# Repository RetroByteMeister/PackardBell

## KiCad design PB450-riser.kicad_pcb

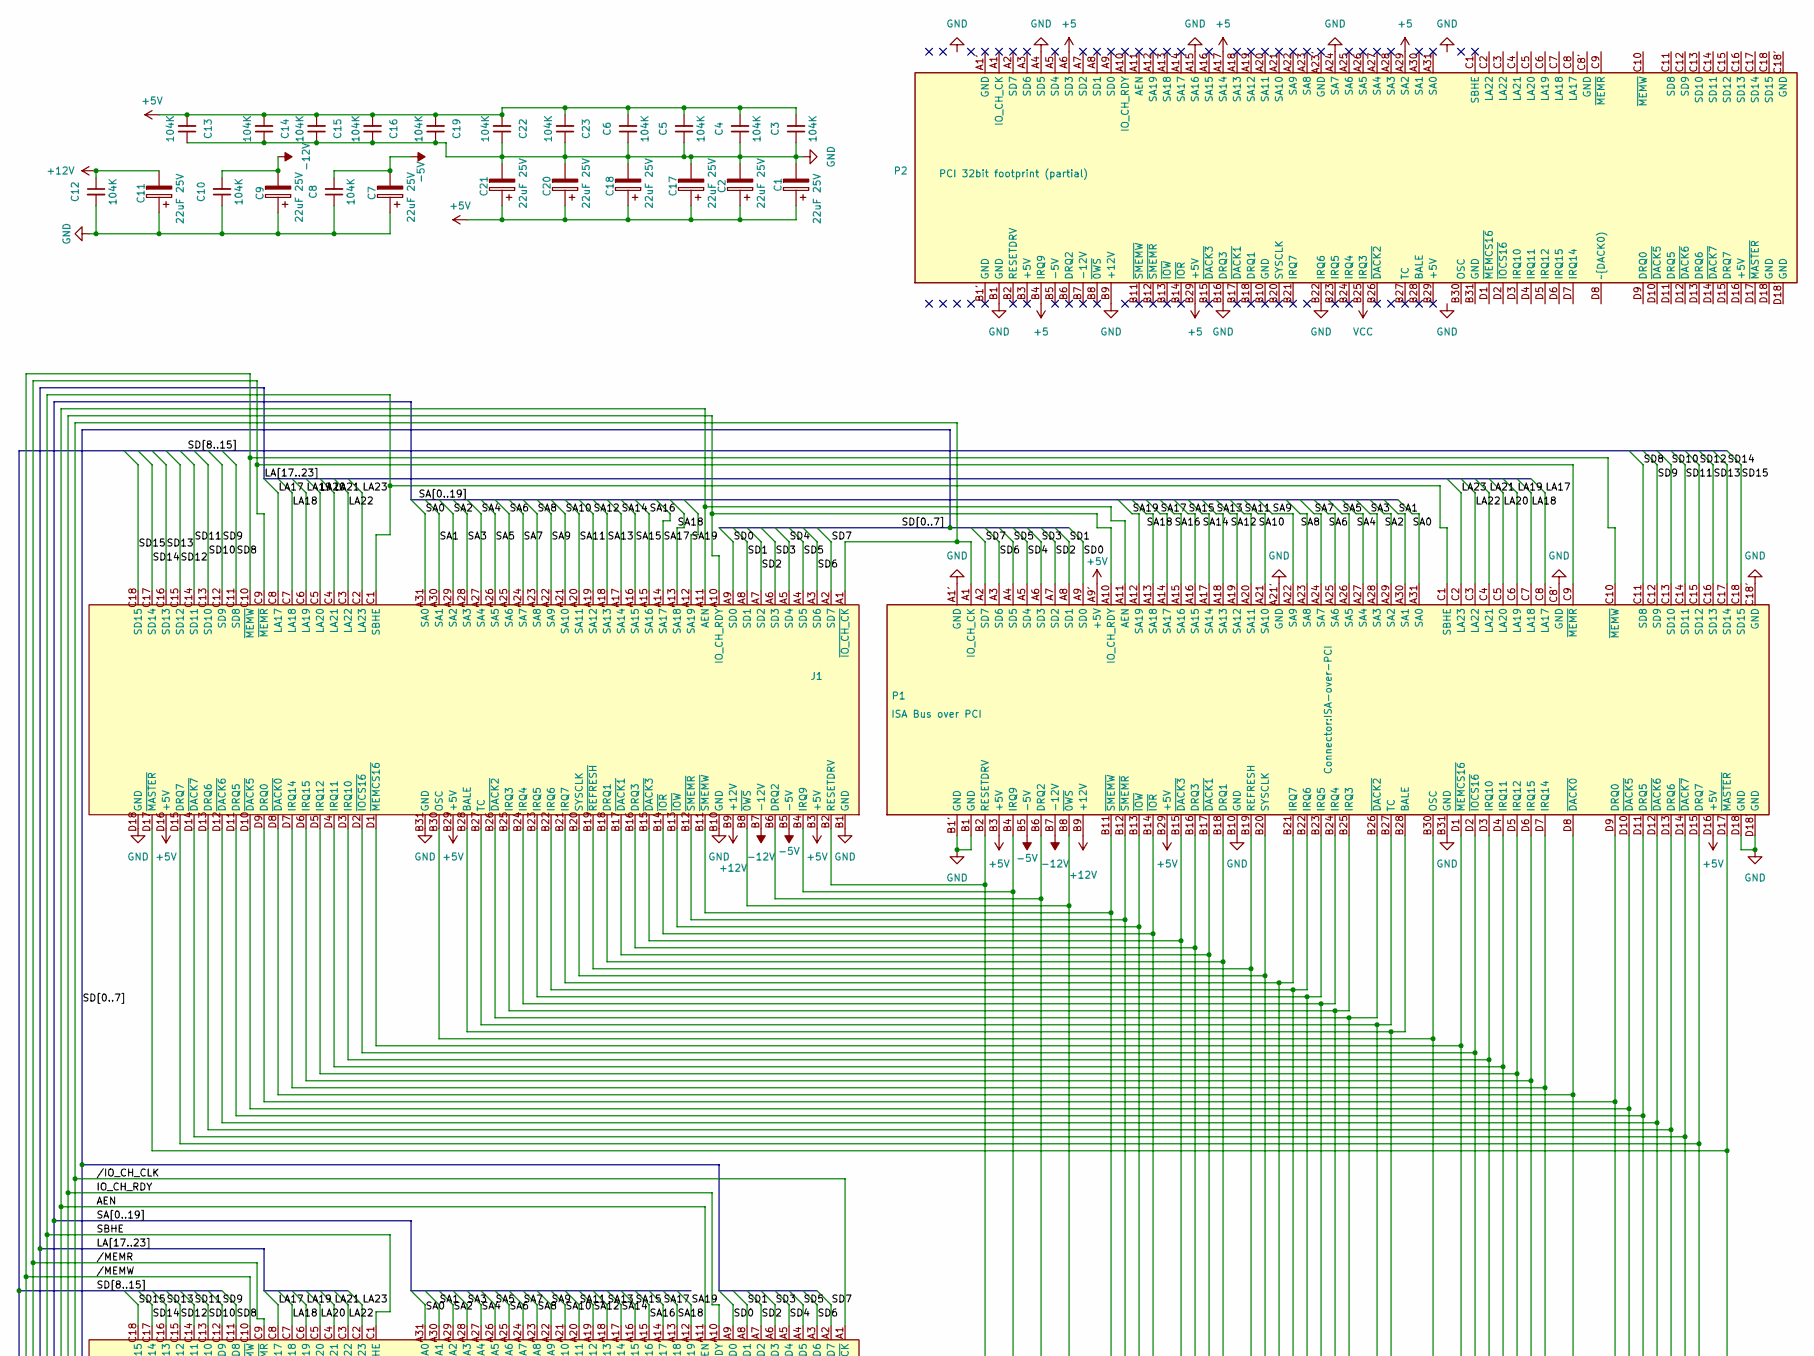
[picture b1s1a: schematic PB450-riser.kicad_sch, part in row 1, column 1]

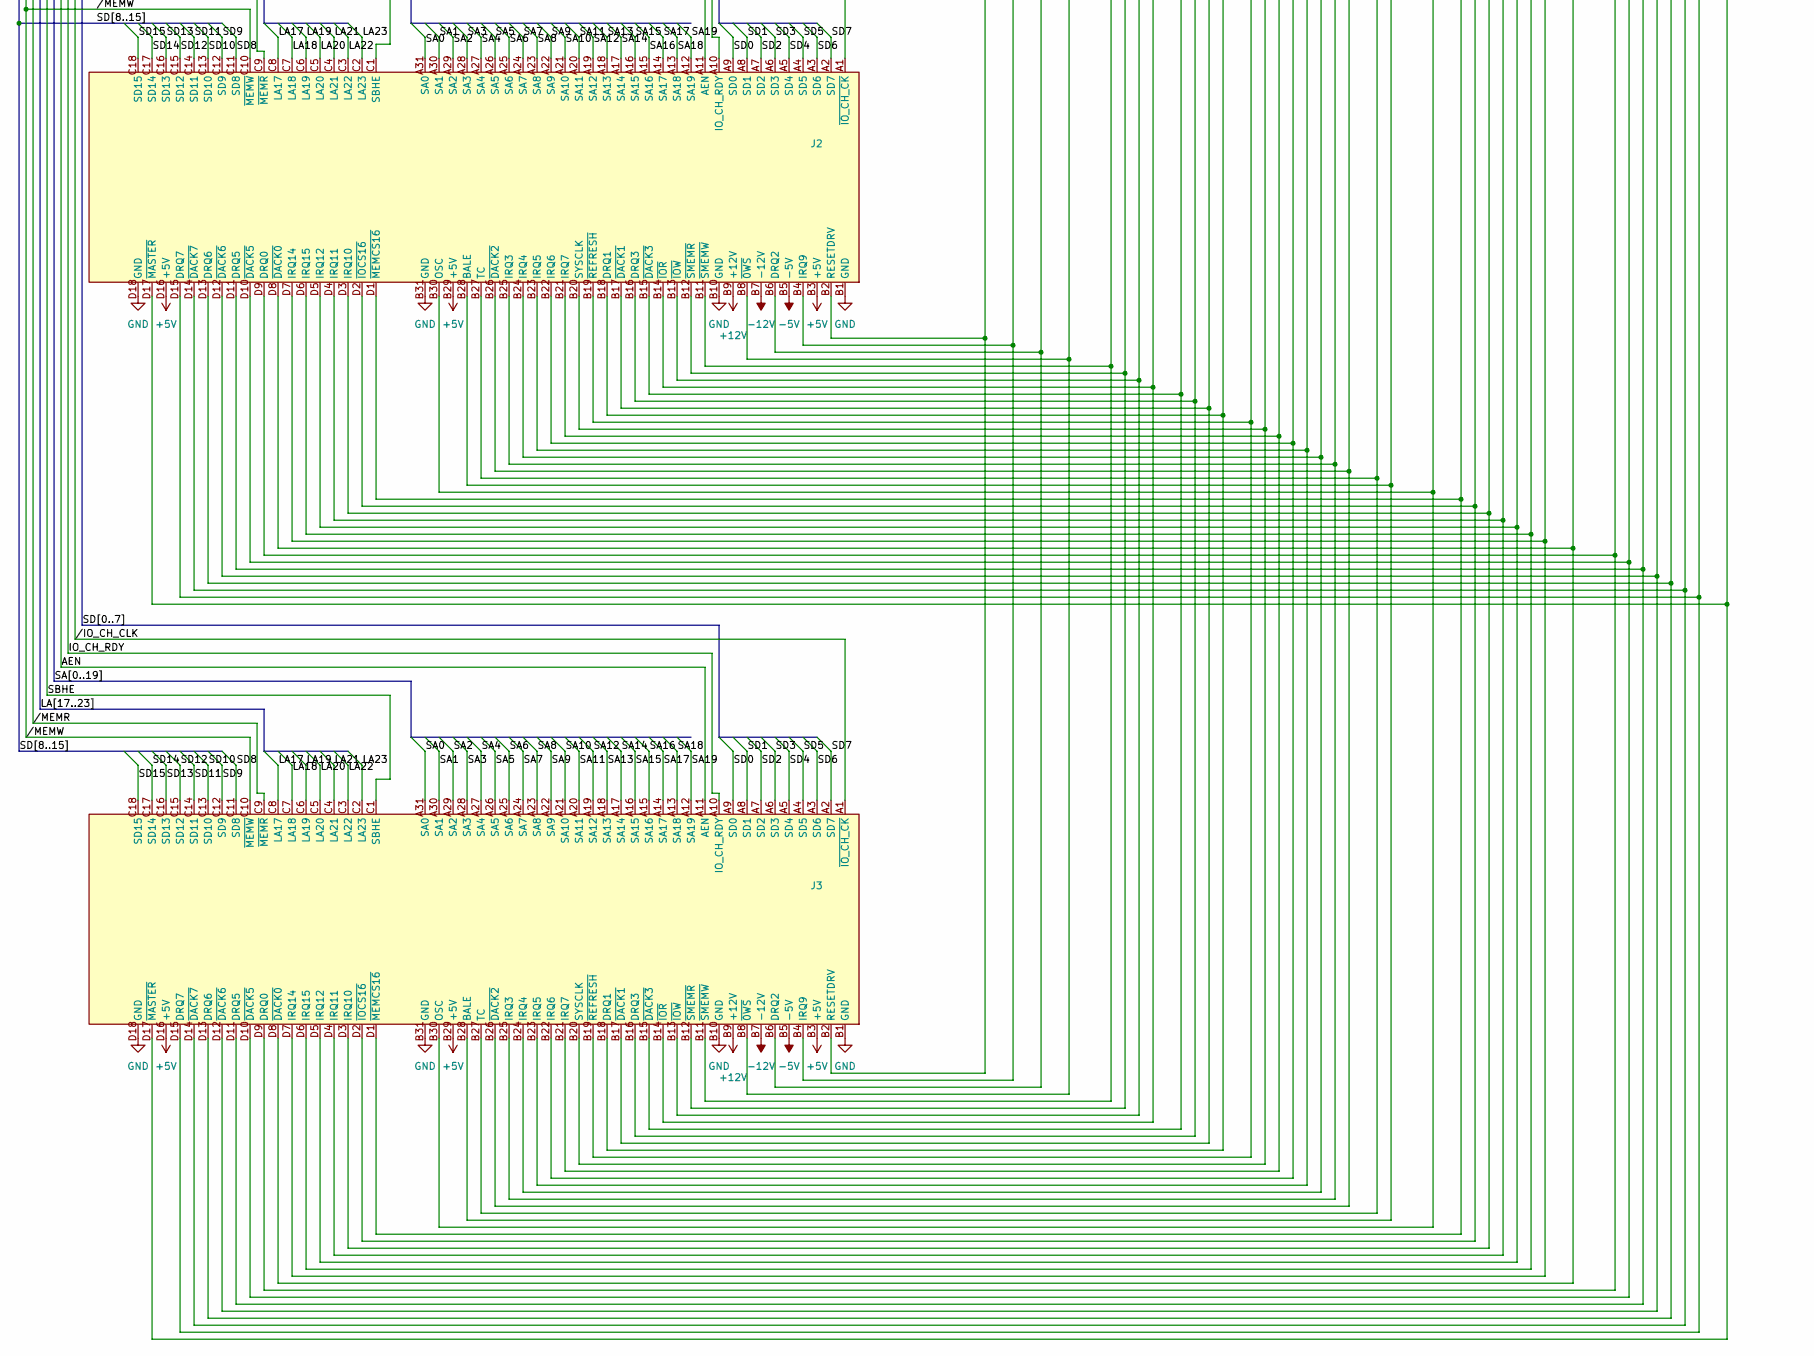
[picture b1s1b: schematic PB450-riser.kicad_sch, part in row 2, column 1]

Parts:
C1, C2, C7, C9, C11, C17, C18, C20, C21: 22uF 25V; CP_Radial_D5.0mm_P2.00mm
C3, C4, C5, C6, C8, C10, C12, C13, C14, C15, C16, C19, C22, C23: 104K; C_Disc_D5.0mm_W2.5mm_P2.50mm
J1, J2, J3: J1; ISA_Mount_Holes
P1: ISA Bus over PCI; ISA-over-PCI
P2: PCI 32bit footprint (partial); BUS_PCI

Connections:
+5V: C1.1, C2.1, C3.2, C4.2, C5.2, C6.2, C13.2, C14.2, C15.2, C16.2, C17.1, C18.1, C19.2, C20.1, C21.1, C22.2, C23.2, J1.B3 (+5V), J1.B29 (+5V), J1.D16 (+5V), J2.B3 (+5V), J2.B29 (+5V), J2.D16 (+5V), J3.B3 (+5V), J3.B29 (+5V), J3.D16 (+5V), P1.A9' (+5V), P1.B3 (+5V), P1.B29 (+5V), P1.D16 (+5V)
+12V: C11.2, C12.1, J1.B9 (+12V), J2.B9 (+12V), J3.B9 (+12V), P1.B9 (+12V)
-5V: C7.2, C8.2, J1.B5 (-5V), J2.B5 (-5V), J3.B5 (-5V), P1.B5 (-5V)
-12V: C9.2, C10.2, J1.B7 (-12V), J2.B7 (-12V), J3.B7 (-12V), P1.B7 (-12V)
/AEN: J1.A11 (AEN), J2.A11 (AEN), J3.A11 (AEN), P1.A11 (AEN)
/IO_CH_RDY: J1.A10 (IO_CH_RDY), J2.A10 (IO_CH_RDY), J3.A10 (IO_CH_RDY), P1.A10 (IO_CH_RDY)
/LA17: J1.C8 (LA17), J2.C8 (LA17), J3.C8 (LA17), P1.C8 (LA17)
/LA18: J1.C7 (LA18), J2.C7 (LA18), J3.C7 (LA18), P1.C7 (LA18)
/LA19: J1.C6 (LA19), J2.C6 (LA19), J3.C6 (LA19), P1.C6 (LA19)
/LA20: J1.C5 (LA20), J2.C5 (LA20), J3.C5 (LA20), P1.C5 (LA20)
/LA21: J1.C4 (LA21), J2.C4 (LA21), J3.C4 (LA21), P1.C4 (LA21)
/LA22: J1.C3 (LA22), J2.C3 (LA22), J3.C3 (LA22), P1.C3 (LA22)
/LA23: J1.C2 (LA23), J2.C2 (LA23), J3.C2 (LA23), P1.C2 (LA23)
/SA0: J1.A31 (SA0), J2.A31 (SA0), J3.A31 (SA0), P1.A31 (SA0)
/SA1: J1.A30 (SA1), J2.A30 (SA1), J3.A30 (SA1), P1.A30 (SA1)
/SA2: J1.A29 (SA2), J2.A29 (SA2), J3.A29 (SA2), P1.A29 (SA2)
/SA3: J1.A28 (SA3), J2.A28 (SA3), J3.A28 (SA3), P1.A28 (SA3)
/SA4: J1.A27 (SA4), J2.A27 (SA4), J3.A27 (SA4), P1.A27 (SA4)
/SA5: J1.A26 (SA5), J2.A26 (SA5), J3.A26 (SA5), P1.A26 (SA5)
/SA6: J1.A25 (SA6), J2.A25 (SA6), J3.A25 (SA6), P1.A25 (SA6)
/SA7: J1.A24 (SA7), J2.A24 (SA7), J3.A24 (SA7), P1.A24 (SA7)
/SA8: J1.A23 (SA8), J2.A23 (SA8), J3.A23 (SA8), P1.A23 (SA8)
/SA9: J1.A22 (SA9), J2.A22 (SA9), J3.A22 (SA9), P1.A22 (SA9)
/SA10: J1.A21 (SA10), J2.A21 (SA10), J3.A21 (SA10), P1.A21 (SA10)
/SA11: J1.A20 (SA11), J2.A20 (SA11), J3.A20 (SA11), P1.A20 (SA11)
/SA12: J1.A19 (SA12), J2.A19 (SA12), J3.A19 (SA12), P1.A19 (SA12)
/SA13: J1.A18 (SA13), J2.A18 (SA13), J3.A18 (SA13), P1.A18 (SA13)
/SA14: J1.A17 (SA14), J2.A17 (SA14), J3.A17 (SA14), P1.A17 (SA14)
/SA15: J1.A16 (SA15), J2.A16 (SA15), J3.A16 (SA15), P1.A16 (SA15)
/SA16: J1.A15 (SA16), J2.A15 (SA16), J3.A15 (SA16), P1.A15 (SA16)
/SA17: J1.A14 (SA17), J2.A14 (SA17), J3.A14 (SA17), P1.A14 (SA17)
/SA18: J1.A13 (SA18), J2.A13 (SA18), J3.A13 (SA18), P1.A13 (SA18)
/SA19: J1.A12 (SA19), J2.A12 (SA19), J3.A12 (SA19), P1.A12 (SA19)
/SBHE: J1.C1 (SBHE), J2.C1 (SBHE), J3.C1 (SBHE), P1.C1 (SBHE)
/SD0: J1.A9 (SD0), J2.A9 (SD0), J3.A9 (SD0), P1.A9 (SD0)
/SD1: J1.A8 (SD1), J2.A8 (SD1), J3.A8 (SD1), P1.A8 (SD1)
/SD2: J1.A7 (SD2), J2.A7 (SD2), J3.A7 (SD2), P1.A7 (SD2)
/SD3: J1.A6 (SD3), J2.A6 (SD3), J3.A6 (SD3), P1.A6 (SD3)
/SD4: J1.A5 (SD4), J2.A5 (SD4), J3.A5 (SD4), P1.A5 (SD4)
/SD5: J1.A4 (SD5), J2.A4 (SD5), J3.A4 (SD5), P1.A4 (SD5)
/SD6: J1.A3 (SD6), J2.A3 (SD6), J3.A3 (SD6), P1.A3 (SD6)
/SD7: J1.A2 (SD7), J2.A2 (SD7), J3.A2 (SD7), P1.A2 (SD7)
/SD8: J1.C11 (SD8), J2.C11 (SD8), J3.C11 (SD8), P1.C11 (SD8)
/SD9: J1.C12 (SD9), J2.C12 (SD9), J3.C12 (SD9), P1.C12 (SD9)
/SD10: J1.C13 (SD10), J2.C13 (SD10), J3.C13 (SD10), P1.C13 (SD10)
/SD11: J1.C14 (SD11), J2.C14 (SD11), J3.C14 (SD11), P1.C14 (SD11)
/SD12: J1.C15 (SD12), J2.C15 (SD12), J3.C15 (SD12), P1.C15 (SD12)
/SD13: J1.C16 (SD13), J2.C16 (SD13), J3.C16 (SD13), P1.C16 (SD13)
/SD14: J1.C17 (SD14), J2.C17 (SD14), J3.C17 (SD14), P1.C17 (SD14)
/SD15: J1.C18 (SD15), J2.C18 (SD15), J3.C18 (SD15), P1.C18 (SD15)
//IO_CH_CLK: J1.A1 (~IO_CH_CK), J2.A1 (~IO_CH_CK), J3.A1 (~IO_CH_CK), P1.A1 (IO_CH_CK)
//MEMR: J1.C9 (~MEMR), J2.C9 (~MEMR), J3.C9 (~MEMR), P1.C9 (~MEMR)
//MEMW: J1.C10 (~MEMW), J2.C10 (~MEMW), J3.C10 (~MEMW), P1.C10 (~MEMW)
GND: C1.2, C2.2, C3.1, C4.1, C5.1, C6.1, C7.1, C8.1, C9.1, C10.1, C11.1, C12.2, C13.1, C14.1, C15.1, C16.1, C17.2, C18.2, C19.1, C20.2, C21.2, C22.1, C23.1, J1.B1 (GND), J1.B10 (GND), J1.B31 (GND), J1.D18 (GND), J2.B1 (GND), J2.B10 (GND), J2.B31 (GND), J2.D18 (GND), J3.B1 (GND), J3.B10 (GND), J3.B31 (GND), J3.D18 (GND), P1.A1' (GND), P1.A21' (GND), P1.B1 (GND), P1.B1' (GND), P1.B10 (GND), P1.B31 (GND), P1.C8' (GND), P1.C18' (GND), P1.D18 (GND), P1.D18' (GND), P2.A4 (SD5), P2.A15 (SA16), P2.A24 (SA7), P2.B1 (GND), P2.B9 (+12V), P2.B16 (DRQ3), P2.B22 (IRQ6)
unnamed: J1.B28 (BALE), J2.B28 (BALE), J3.B28 (BALE), P1.B28 (BALE)
unnamed: J1.D9 (DRQ0), J2.D9 (DRQ0), J3.D9 (DRQ0), P1.D9 (DRQ0)
unnamed: J1.B18 (DRQ1), J2.B18 (DRQ1), J3.B18 (DRQ1), P1.B18 (DRQ1)
unnamed: J1.B6 (DRQ2), J2.B6 (DRQ2), J3.B6 (DRQ2), P1.B6 (DRQ2)
unnamed: J1.B16 (DRQ3), J2.B16 (DRQ3), J3.B16 (DRQ3), P1.B16 (DRQ3)
unnamed: J1.D11 (DRQ5), J2.D11 (DRQ5), J3.D11 (DRQ5), P1.D11 (DRQ5)
unnamed: J1.D13 (DRQ6), J2.D13 (DRQ6), J3.D13 (DRQ6), P1.D13 (DRQ6)
unnamed: J1.D15 (DRQ7), J2.D15 (DRQ7), J3.D15 (DRQ7), P1.D15 (DRQ7)
unnamed: J1.B25 (IRQ3), J2.B25 (IRQ3), J3.B25 (IRQ3), P1.B25 (IRQ3)
unnamed: J1.B24 (IRQ4), J2.B24 (IRQ4), J3.B24 (IRQ4), P1.B24 (IRQ4)
unnamed: J1.B23 (IRQ5), J2.B23 (IRQ5), J3.B23 (IRQ5), P1.B23 (IRQ5)
unnamed: J1.B22 (IRQ6), J2.B22 (IRQ6), J3.B22 (IRQ6), P1.B22 (IRQ6)
unnamed: J1.B21 (IRQ7), J2.B21 (IRQ7), J3.B21 (IRQ7), P1.B21 (IRQ7)
unnamed: J1.B4 (IRQ9), J2.B4 (IRQ9), J3.B4 (IRQ9), P1.B4 (IRQ9)
unnamed: J1.D3 (IRQ10), J2.D3 (IRQ10), J3.D3 (IRQ10), P1.D3 (IRQ10)
unnamed: J1.D4 (IRQ11), J2.D4 (IRQ11), J3.D4 (IRQ11), P1.D4 (IRQ11)
unnamed: J1.D5 (IRQ12), J2.D5 (IRQ12), J3.D5 (IRQ12), P1.D5 (IRQ12)
unnamed: J1.D7 (IRQ14), J2.D7 (IRQ14), J3.D7 (IRQ14), P1.D7 (IRQ14)
unnamed: J1.D6 (IRQ15), J2.D6 (IRQ15), J3.D6 (IRQ15), P1.D6 (IRQ15)
unnamed: J1.B30 (OSC), J2.B30 (OSC), J3.B30 (OSC), P1.B30 (OSC)
unnamed: J1.B2 (RESETDRV), J2.B2 (RESETDRV), J3.B2 (RESETDRV), P1.B2 (RESETDRV)
unnamed: J1.B20 (SYSCLK), J2.B20 (SYSCLK), J3.B20 (SYSCLK), P1.B20 (SYSCLK)
unnamed: J1.B27 (TC), J2.B27 (TC), J3.B27 (TC), P1.B27 (TC)
unnamed: J1.B8 (~0WS), J2.B8 (~0WS), J3.B8 (~0WS), P1.B8 (~0WS)
unnamed: J1.D8 (~DACK0), J2.D8 (~DACK0), J3.D8 (~DACK0), P1.D8 (~DACK0)
unnamed: J1.B17 (~DACK1), J2.B17 (~DACK1), J3.B17 (~DACK1), P1.B17 (~DACK1)
unnamed: J1.B26 (~DACK2), J2.B26 (~DACK2), J3.B26 (~DACK2), P1.B26 (~DACK2)
unnamed: J1.B15 (~DACK3), J2.B15 (~DACK3), J3.B15 (~DACK3), P1.B15 (~DACK3)
unnamed: J1.D10 (~DACK5), J2.D10 (~DACK5), J3.D10 (~DACK5), P1.D10 (~DACK5)
unnamed: J1.D12 (~DACK6), J2.D12 (~DACK6), J3.D12 (~DACK6), P1.D12 (~DACK6)
unnamed: J1.D14 (~DACK7), J2.D14 (~DACK7), J3.D14 (~DACK7), P1.D14 (~DACK7)
unnamed: J1.D2 (~IOCS16), J2.D2 (~IOCS16), J3.D2 (~IOCS16), P1.D2 (~IOCS16)
unnamed: J1.B14 (~IOR), J2.B14 (~IOR), J3.B14 (~IOR), P1.B14 (~IOR)
unnamed: J1.B13 (~IOW), J2.B13 (~IOW), J3.B13 (~IOW), P1.B13 (~IOW)
unnamed: J1.D17 (~MASTER), J2.D17 (~MASTER), J3.D17 (~MASTER), P1.D17 (~MASTER)
unnamed: J1.D1 (~MEMCS16), J2.D1 (~MEMCS16), J3.D1 (~MEMCS16), P1.D1 (~MEMCS16)
unnamed: J1.B19 (~REFRESH), J2.B19 (~REFRESH), J3.B19 (~REFRESH), P1.B19 (REFRESH)
unnamed: J1.B12 (~SMEMR), J2.B12 (~SMEMR), J3.B12 (~SMEMR), P1.B12 (~SMEMR)
unnamed: J1.B11 (~SMEMW), J2.B11 (~SMEMW), J3.B11 (~SMEMW), P1.B11 (~SMEMW)
unnamed: P2.A6 (SD3), P2.A17 (SA14), P2.A29 (SA2), P2.B4 (IRQ9), P2.B29 (+5V)

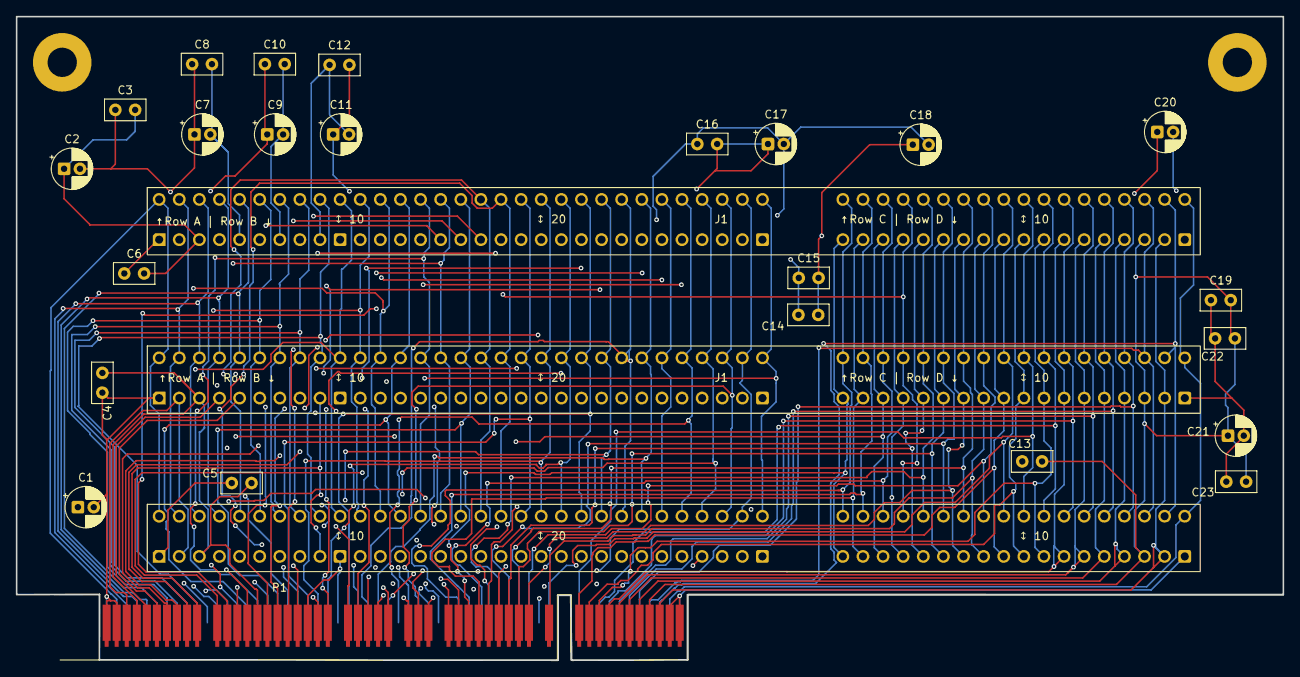
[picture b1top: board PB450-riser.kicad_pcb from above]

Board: 4 copper layers, 160.0 x 81.3 mm, 27 parts (0 on the bottom side), 93 nets.

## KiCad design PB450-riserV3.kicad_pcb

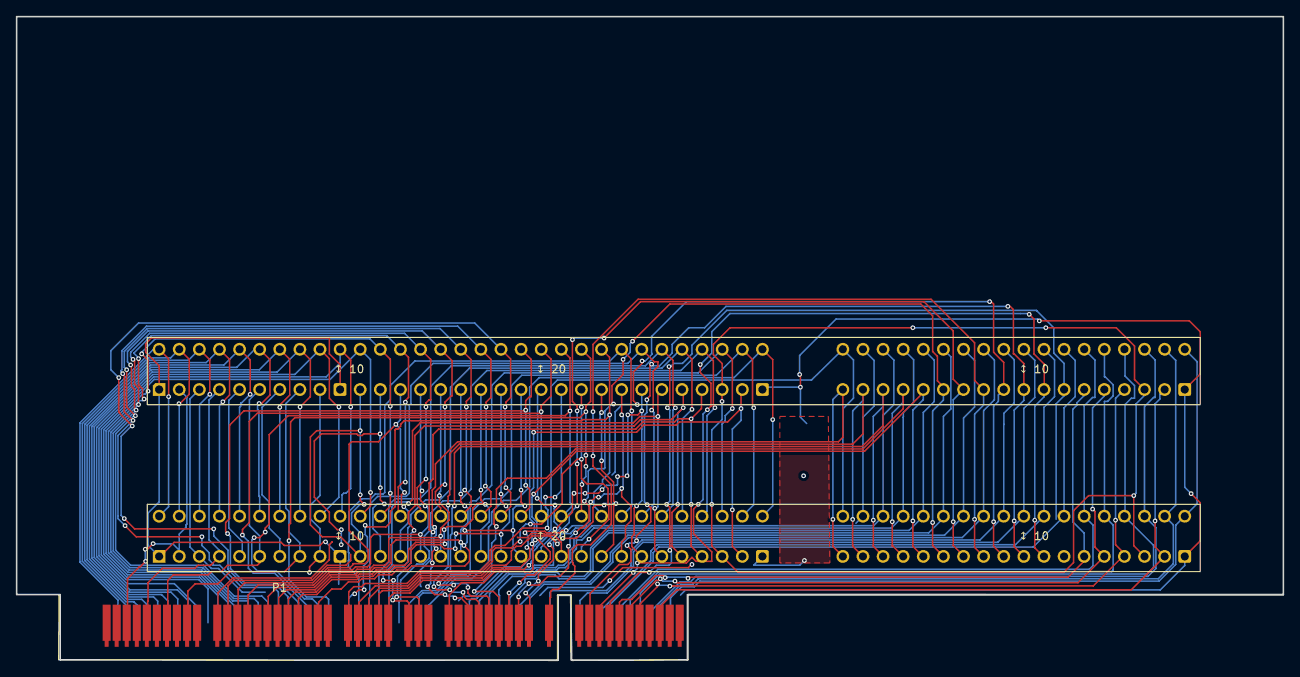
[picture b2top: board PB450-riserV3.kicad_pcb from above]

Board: 2 copper layers, 160.0 x 81.3 mm, 3 parts (0 on the bottom side), 49 nets.

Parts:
J1, J2: J1; ISA_Mount_Holes
P1: ISA Bus over PCI; BUS_ISA-over-PCI

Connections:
+5V: J1.B3 (+5V), J1.B29 (+5V), J1.D16 (+5V), P1.B3 (+5V), P1.B29 (+5V), P1.D16 (+5V)
+12V: J1.B9 (+12V), P1.B9 (+12V)
-5V: J1.B5 (-5V), P1.B5 (-5V)
-12V: J1.B7 (-12V), P1.B7 (-12V)
GND: J1.B1 (GND), J1.B10 (GND), J1.B31 (GND), J1.D18 (GND), P1.A1' (GND), P1.A22' (GND), P1.B1 (GND), P1.B1' (GND), P1.B10 (GND), P1.B31 (GND), P1.C8' (GND), P1.C18' (GND), P1.D18 (GND), P1.D18' (GND)
unnamed: J1.A11 (AEN), P1.A11 (AEN)
unnamed: J1.D9 (DRQ0), P1.D9 (DRQ0)
unnamed: J1.B18 (DRQ1), P1.B18 (DRQ1)
unnamed: J1.B6 (DRQ2), P1.B6 (DRQ2)
unnamed: J1.B16 (DRQ3), P1.B16 (DRQ3)
unnamed: J1.D11 (DRQ5), P1.D11 (DRQ5)
unnamed: J1.D13 (DRQ6), P1.D13 (DRQ6)
unnamed: J1.D15 (DRQ7), P1.D15 (DRQ7)
unnamed: J1.A10 (IO_CH_RDY), P1.A10 (IO_CH_RDY)
unnamed: J1.B25 (IRQ3), P1.B26 (~DACK2)
unnamed: J1.B24 (IRQ4), P1.B25 (IRQ3)
unnamed: J1.B23 (IRQ5), P1.B24 (IRQ4)
unnamed: J1.B22 (IRQ6), P1.B23 (IRQ5)
unnamed: J1.B21 (IRQ7), P1.B22 (IRQ6)
unnamed: J1.B4 (IRQ9), P1.B4 (IRQ9)
unnamed: J1.D3 (IRQ10), P1.D3 (IRQ10)
unnamed: J1.D4 (IRQ11), P1.D4 (IRQ11)
unnamed: J1.D5 (IRQ12), P1.D5 (IRQ12)
unnamed: J1.D7 (IRQ14), P1.D7 (IRQ14)
unnamed: J1.D6 (IRQ15), P1.D6 (IRQ15)
unnamed: J1.B30 (OSC), P1.B30 (OSC)
unnamed: J1.B2 (RESETDRV), P1.B2 (RESETDRV)
unnamed: J1.C1 (SBHE), P1.C1 (SBHE)
unnamed: J1.B20 (SYSCLK), P1.B21 (IRQ7)
unnamed: J1.B27 (TC), P1.B28 (BALE)
unnamed: J1.B8 (~0WS), P1.B8 (~0WS)
unnamed: J1.D8 (~DACK0), P1.D8 (~{DACK0))
unnamed: J1.B17 (~DACK1), P1.B17 (~DACK1)
unnamed: J1.B26 (~DACK2), P1.B27 (TC)
unnamed: J1.B15 (~DACK3), P1.B15 (~DACK3)
unnamed: J1.D10 (~DACK5), P1.D10 (~DACK5)
unnamed: J1.D12 (~DACK6), P1.D12 (~DACK6)
unnamed: J1.D14 (~DACK7), P1.D14 (~DACK7)
unnamed: J1.D2 (~IOCS16), P1.D2 (~IOCS16)
unnamed: J1.B14 (~IOR), P1.B14 (~IOR)
unnamed: J1.B13 (~IOW), P1.B13 (~IOW)
unnamed: J1.A1 (~IO_CH_CK), P1.A1 (IO_CH_CK)
unnamed: J1.D17 (~MASTER), P1.D17 (~MASTER)
unnamed: J1.D1 (~MEMCS16), P1.D1 (~MEMCS16)
unnamed: J1.C9 (~MEMR), P1.C9 (~MEMR)
unnamed: J1.C10 (~MEMW), P1.C10 (~MEMW)
unnamed: J1.B19 (~REFRESH), P1.B20 (SYSCLK)
unnamed: J1.B12 (~SMEMR), P1.B12 (~SMEMR)
unnamed: J1.B11 (~SMEMW), P1.B11 (~SMEMW)
